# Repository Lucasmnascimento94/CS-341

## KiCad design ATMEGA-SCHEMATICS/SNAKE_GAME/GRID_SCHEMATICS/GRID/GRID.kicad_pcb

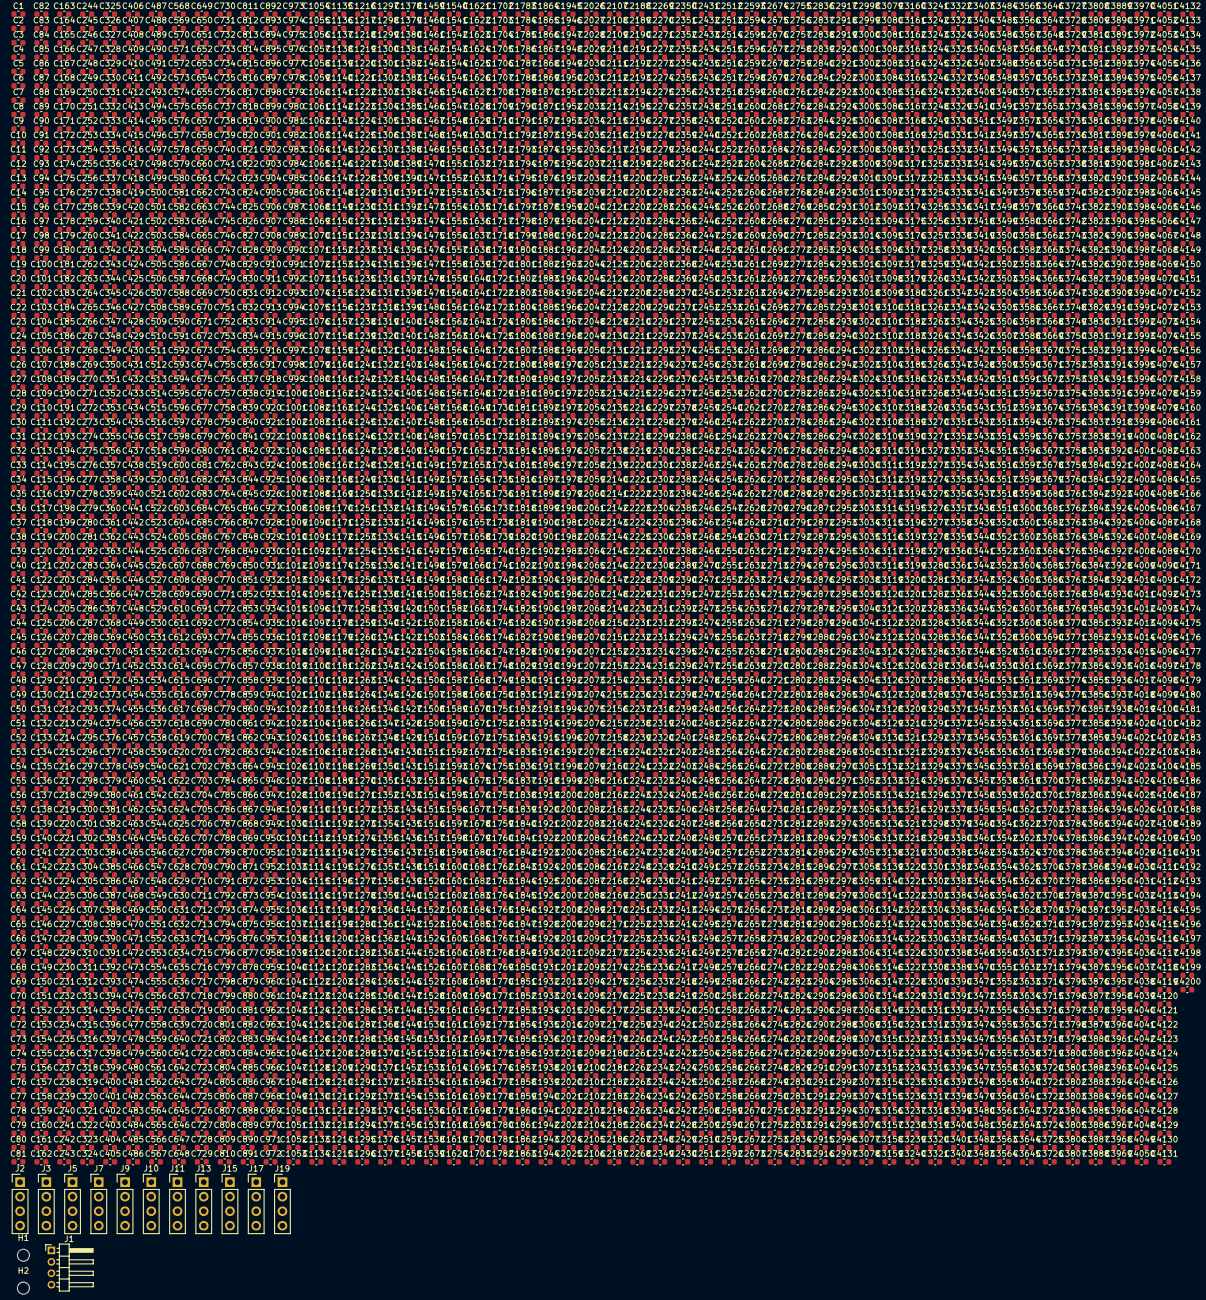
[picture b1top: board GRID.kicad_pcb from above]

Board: 4 copper layers, 4216 parts (0 on the bottom side), 13 nets, no tracks yet.

Parts (part):
C1, C2, C3, C4, C5, C6, C7, C8, C9, C10, C11, C12, C13, C14, C15, C16, C17, C18, C19, C20, C21, C22, C23, C24, C25, C26, C27, C28, C29, C30, C31, C32, C33, C34, C35, C36, C37, C38, C39, C40, C41, C42, C43, C44, C45, C46, C47, C48, C49, C50, C51, C52, C53, C54, C55, C56, C57, C58, C59, C60, C61, C62, C63, C64, C65, C66, C67, C68, C69, C70, C71, C72, C73, C74, C75, C76, C77, C78, C79, C80, C81, C82, C83, C84, C85, C86, C87, C88, C89, C90, C91, C92, C93, C94, C95, C96, C97, C98, C99, C100, C101, C102, C103, C104, C105, C106, C107, C108, C109, C110, C111, C112, C113, C114, C115, C116, C117, C118, C119, C120, C121, C122, C123, C124, C125, C126, C127, C128, C129, C130, C131, C132, C133, C134, C135, C136, C137, C138, C139, C140, C141, C142, C143, C144, C145, C146, C147, C148, C149, C150, C151, C152, C153, C154, C155, C156, C157, C158, C159, C160, C161, C162, C163, C164, C165, C166, C167, C168, C169, C170, C171, C172, C173, C174, C175, C176, C177, C178, C179, C180, C181, C182, C183, C184, C185, C186, C187, C188, C189, C190, C191, C192, C193, C194, C195, C196, C197, C198, C199, C200, C201, C202, C203, C204, C205, C206, C207, C208, C209, C210, C211, C212, C213, C214, C215, C216, C217, C218, C219, C220, C221, C222, C223, C224, C225, C226, C227, C228, C229, C230, C231, C232, C233, C234, C235, C236, C237, C238, C239, C240, C241, C242, C243, C244, C245, C246, C247, C248, C249, C250, C251, C252, C253, C254, C255, C256, C257, C258, C259, C260, C261, C262, C263, C264, C265, C266, C267, C268, C269, C270, C271, C272, C273, C274, C275, C276, C277, C278, C279, C280, C281, C282, C283, C284, C285, C286, C287, C288, C289, C290, C291, C292, C293, C294, C295, C296, C297, C298, C299, C300, C301, C302, C303, C304, C305, C306, C307, C308, C309, C310, C311, C312, C313, C314, C315, C316, C317, C318, C319, C320, C321, C322, C323, C324, C325, C326, C327, C328, C329, C330, C331, C332, C333, C334, C335, C336, C337, C338, C339, C340, C341, C342, C343, C344, C345, C346, C347, C348, C349, C350, C351, C352, C353, C354, C355, C356, C357, C358, C359, C360, C361, C362, C363, C364, C365, C366, C367, C368, C369, C370, C371, C372, C373, C374, C375, C376, C377, C378, C379, C380, C381, C382, C383, C384, C385, C386, C387, C388, C389, C390, C391, C392, C393, C394, C395, C396, C397, C398, C399, C400, C401, C402, C403, C404, C405, C406, C407, C408, C409, C410, C411, C412, C413, C414, C415, C416, C417, C418, C419, C420, C421, C422, C423, C424, C425, C426, C427, C428, C429, C430, C431, C432, C433, C434, C435, C436, C437, C438, C439, C440, C441, C442, C443, C444, C445, C446, C447, C448, C449, C450, C451, C452, C453, C454, C455, C456, C457, C458, C459, C460, C461, C462, C463, C464, C465, C466, C467, C468, C469, C470, C471, C472, C473, C474, C475, C476, C477, C478, C479, C480, C481, C482, C483, C484, C485, C486, C487, C488, C489, C490, C491, C492, C493, C494, C495, C496, C497, C498, C499, C500, C501, C502, C503, C504, C505, C506, C507, C508, C509, C510, C511, C512, C513, C514, C515, C516, C517, C518, C519, C520, C521, C522, C523, C524, C525, C526, C527, C528, C529, C530, C531, C532, C533, C534, C535, C536, C537, C538, C539, C540, C541, C542, C543, C544, C545, C546, C547, C548, C549, C550, C551, C552, C553, C554, C555, C556, C557, C558, C559, C560, C561, C562, C563, C564, C565, C566, C567, C568, C569, C570, C571, C572, C573, C574, C575, C576, C577, C578, C579, C580, C581, C582, C583, C584, C585, C586, C587, C588, C589, C590, C591, C592, C593, C594, C595, C596, C597, C598, C599, C600, C601, C602, C603, C604, C605, C606, C607, C608, C609, C610, C611, C612, C613, C614, C615, C616, C617, C618, C619, C620, C621, C622, C623, C624, C625, C626, C627, C628, C629, C630, C631, C632, C633, C634, C635, C636, C637, C638, C639, C640, C641, C642, C643, C644, C645, C646, C647, C648, C649, C650, C651, C652, C653, C654, C655, C656, C657, C658, C659, C660, C661, C662, C663, C664, C665, C666, C667, C668, C669, C670, C671, C672, C673, C674, C675, C676, C677, C678, C679, C680, C681, C682, C683, C684, C685, C686, C687, C688, C689, C690, C691, C692, C693, C694, C695, C696, C697, C698, C699, C700, C701, C702, C703, C704, C705, C706, C707, C708, C709, C710, C711, C712, C713, C714, C715, C716, C717, C718, C719, C720, C721, C722, C723, C724, C725, C726, C727, C728, C729, C730, C731, C732, C733, C734, C735, C736, C737, C738, C739, C740, C741, C742, C743, C744, C745, C746, C747, C748, C749, C750, C751, C752, C753, C754, C755, C756, C757, C758, C759, C760, C761, C762, C763, C764, C765, C766, C767, C768, C769, C770, C771, C772, C773, C774, C775, C776, C777, C778, C779, C780, C781, C782, C783, C784, C785, C786, C787, C788, C789, C790, C791, C792, C793, C794, C795, C796, C797, C798, C799, C800, C801, C802, C803, C804, C805, C806, C807, C808, C809, C810, C811, C812, C813, C814, C815, C816, C817, C818, C819, C820, C821, C822, C823, C824, C825, C826, C827, C828, C829, C830, C831, C832, C833, C834, C835, C836, C837, C838, C839, C840, C841, C842, C843, C844, C845, C846, C847, C848, C849, C850, C851, C852, C853, C854, C855, C856, C857, C858, C859, C860, C861, C862, C863, C864, C865, C866, C867, C868, C869, C870, C871, C872, C873, C874, C875, C876, C877, C878, C879, C880, C881, C882, C883, C884, C885, C886, C887, C888, C889, C890, C891, C892, C893, C894, C895, C896, C897, C898, C899, C900, C901, C902, C903, C904, C905, C906, C907, C908, C909, C910, C911, C912, C913, C914, C915, C916, C917, C918, C919, C920, C921, C922, C923, C924, C925, C926, C927, C928, C929, C930, C931, C932, C933, C934, C935, C936, C937, C938, C939, C940, C941, C942, C943, C944, C945, C946, C947, C948, C949, C950, C951, C952, C953, C954, C955, C956, C957, C958, C959, C960, C961, C962, C963, C964, C965, C966, C967, C968, C969, C970, C971, C972, C973, C974, C975, C976, C977, C978, C979, C980, C981, C982, C983, C984, C985, C986, C987, C988, C989, C990, C991, C992, C993, C994, C995, C996, C997, C998, C999, C1000, C1001, C1002, C1003, C1004, C1005, C1006, C1007, C1008, C1009, C1010, C1011, C1012, C1013, C1014, C1015, C1016, C1017, C1018, C1019, C1020, C1021, C1022, C1023, C1024, C1025, C1026, C1027, C1028, C1029, C1030, C1031, C1032, C1033, C1034, C1035, C1036, C1037, C1038, C1039, C1040, C1041, C1042, C1043, C1044, C1045, C1046, C1047, C1048, C1049, C1050, C1051, C1052, C1053, C1054, C1055, C1056, C1057, C1058, C1059, C1060, C1061, C1062, C1063, C1064, C1065, C1066, C1067, C1068, C1069, C1070, C1071, C1072, C1073, C1074, C1075, C1076, C1077, C1078, C1079, C1080, C1081, C1082, C1083, C1084, C1085, C1086, C1087, C1088, C1089, C1090, C1091, C1092, C1093, C1094, C1095, C1096, C1097, C1098, C1099, C1100, C1101, C1102, C1103, C1104, C1105, C1106, C1107, C1108, C1109, C1110, C1111, C1112, C1113, C1114, C1115, C1116, C1117, C1118, C1119, C1120, C1121, C1122, C1123, C1124, C1125, C1126, C1127, C1128, C1129, C1130, C1131, C1132, C1133, C1134, C1135, C1136, C1137, C1138, C1139, C1140, C1141, C1142, C1143, C1144, C1145, C1146, C1147, C1148, C1149, C1150, C1151, C1152, C1153, C1154, C1155, C1156, C1157, C1158, C1159, C1160, C1161, C1162, C1163, C1164, C1165, C1166, C1167, C1168, C1169, C1170, C1171, C1172, C1173, C1174, C1175, C1176, C1177, C1178, C1179, C1180, C1181, C1182, C1183, C1184, C1185, C1186, C1187, C1188, C1189, C1190, C1191, C1192, C1193, C1194, C1195, C1196, C1197, C1198, C1199, C1200, C1201, C1202, C1203, C1204, C1205, C1206, C1207, C1208, C1209, C1210, C1211, C1212, C1213, C1214, C1215, C1216, C1217, C1218, C1219, C1220, C1221, C1222, C1223, C1224, C1225, C1226, C1227, C1228, C1229, C1230, C1231, C1232, C1233, C1234, C1235, C1236, C1237, C1238, C1239, C1240, C1241, C1242, C1243, C1244, C1245, C1246, C1247, C1248, C1249, C1250, C1251, C1252, C1253, C1254, C1255, C1256, C1257, C1258, C1259, C1260, C1261, C1262, C1263, C1264, C1265, C1266, C1267, C1268, C1269, C1270, C1271, C1272, C1273, C1274, C1275, C1276, C1277, C1278, C1279, C1280, C1281, C1282, C1283, C1284, C1285, C1286, C1287, C1288, C1289, C1290, C1291, C1292, C1293, C1294, C1295, C1296, C1297, C1298, C1299, C1300, C1301, C1302, C1303, C1304, C1305, C1306, C1307, C1308, C1309, C1310, C1311, C1312, C1313, C1314, C1315, C1316, C1317, C1318, C1319, C1320, C1321, C1322, C1323, C1324, C1325, C1326, C1327, C1328, C1329, C1330, C1331, C1332, C1333, C1334, C1335, C1336, C1337, C1338, C1339, C1340, C1341, C1342, C1343, C1344, C1345, C1346, C1347, C1348, C1349, C1350, C1351, C1352, C1353, C1354, C1355, C1356, C1357, C1358, C1359, C1360, C1361, C1362, C1363, C1364, C1365, C1366, C1367, C1368, C1369, C1370, C1371, C1372, C1373, C1374, C1375, C1376, C1377, C1378, C1379, C1380, C1381, C1382, C1383, C1384, C1385, C1386, C1387, C1388, C1389, C1390, C1391, C1392, C1393, C1394, C1395, C1396, C1397, C1398, C1399, C1400, C1401, C1402, C1403, C1404, C1405, C1406, C1407, C1408, C1409, C1410, C1411, C1412, C1413, C1414, C1415, C1416, C1417, C1418, C1419, C1420, C1421, C1422, C1423, C1424, C1425, C1426, C1427, C1428, C1429, C1430, C1431, C1432, C1433, C1434, C1435, C1436, C1437, C1438, C1439, C1440, C1441, C1442, C1443, C1444, C1445, C1446, C1447, C1448, C1449, C1450, C1451, C1452, C1453, C1454, C1455, C1456, C1457, C1458, C1459, C1460, C1461, C1462, C1463, C1464, C1465, C1466, C1467, C1468, C1469, C1470, C1471, C1472, C1473, C1474, C1475, C1476, C1477, C1478, C1479, C1480, C1481, C1482, C1483, C1484, C1485, C1486, C1487, C1488, C1489, C1490, C1491, C1492, C1493, C1494, C1495, C1496, C1497, C1498, C1499, C1500, C1501, C1502, C1503, C1504, C1505, C1506, C1507, C1508, C1509, C1510, C1511, C1512, C1513, C1514, C1515, C1516, C1517, C1518, C1519, C1520, C1521, C1522, C1523, C1524, C1525, C1526, C1527, C1528, C1529, C1530, C1531, C1532, C1533, C1534, C1535, C1536, C1537, C1538, C1539, C1540, C1541, C1542, C1543, C1544, C1545, C1546, C1547, C1548, C1549, C1550, C1551, C1552, C1553, C1554, C1555, C1556, C1557, C1558, C1559, C1560, C1561, C1562, C1563, C1564, C1565, C1566, C1567, C1568, C1569, C1570, C1571, C1572, C1573, C1574, C1575, C1576, C1577, C1578, C1579, C1580, C1581, C1582, C1583, C1584, C1585, C1586, C1587, C1588, C1589, C1590, C1591, C1592, C1593, C1594, C1595, C1596, C1597, C1598, C1599, C1600, C1601, C1602, C1603, C1604, C1605, C1606, C1607, C1608, C1609, C1610, C1611, C1612, C1613, C1614, C1615, C1616, C1617, C1618, C1619, C1620, C1621, C1622, C1623, C1624, C1625, C1626, C1627, C1628, C1629, C1630, C1631, C1632, C1633, C1634, C1635, C1636, C1637, C1638, C1639, C1640, C1641, C1642, C1643, C1644, C1645, C1646, C1647, C1648, C1649, C1650, C1651, C1652, C1653, C1654, C1655, C1656, C1657, C1658, C1659, C1660, C1661, C1662, C1663, C1664, C1665, C1666, C1667, C1668, C1669, C1670, C1671, C1672, C1673, C1674, C1675, C1676, C1677, C1678, C1679, C1680, C1681, C1682, C1683, C1684, C1685, C1686, C1687, C1688, C1689, C1690, C1691, C1692, C1693, C1694, C1695, C1696, C1697, C1698, C1699, C1700, C1701, C1702, C1703, C1704, C1705, C1706, C1707, C1708, C1709, C1710, C1711, C1712, C1713, C1714, C1715, C1716, C1717, C1718, C1719, C1720, C1721, C1722, C1723, C1724, C1725, C1726, C1727, C1728, C1729, C1730, C1731, C1732, C1733, C1734, C1735, C1736, C1737, C1738, C1739, C1740, C1741, C1742, C1743, C1744, C1745, C1746, C1747, C1748, C1749, C1750, C1751, C1752, C1753, C1754, C1755, C1756, C1757, C1758, C1759, C1760, C1761, C1762, C1763, C1764, C1765, C1766, C1767, C1768, C1769, C1770, C1771, C1772, C1773, C1774, C1775, C1776, C1777, C1778, C1779, C1780, C1781, C1782, C1783, C1784, C1785, C1786, C1787, C1788, C1789, C1790, C1791, C1792, C1793, C1794, C1795, C1796, C1797, C1798, C1799, C1800, C1801, C1802, C1803, C1804, C1805, C1806, C1807, C1808, C1809, C1810, C1811, C1812, C1813, C1814, C1815, C1816, C1817, C1818, C1819, C1820, C1821, C1822, C1823, C1824, C1825, C1826, C1827, C1828, C1829, C1830, C1831, C1832, C1833, C1834, C1835, C1836, C1837, C1838, C1839, C1840, C1841, C1842, C1843, C1844, C1845, C1846, C1847, C1848, C1849, C1850, C1851, C1852, C1853, C1854, C1855, C1856, C1857, C1858, C1859, C1860, C1861, C1862, C1863, C1864, C1865, C1866, C1867, C1868, C1869, C1870, C1871, C1872, C1873, C1874, C1875, C1876, C1877, C1878, C1879, C1880, C1881, C1882, C1883, C1884, C1885, C1886, C1887, C1888, C1889, C1890, C1891, C1892, C1893, C1894, C1895, C1896, C1897, C1898, C1899, C1900, C1901, C1902, C1903, C1904, C1905, C1906, C1907, C1908, C1909, C1910, C1911, C1912, C1913, C1914, C1915, C1916, C1917, C1918, C1919, C1920, C1921, C1922, C1923, C1924, C1925, C1926, C1927, C1928, C1929, C1930, C1931, C1932, C1933, C1934, C1935, C1936, C1937, C1938, C1939, C1940, C1941, C1942, C1943, C1944, C1945, C1946, C1947, C1948, C1949, C1950, C1951, C1952, C1953, C1954, C1955, C1956, C1957, C1958, C1959, C1960, C1961, C1962, C1963, C1964, C1965, C1966, C1967, C1968, C1969, C1970, C1971, C1972, C1973, C1974, C1975, C1976, C1977, C1978, C1979, C1980, C1981, C1982, C1983, C1984, C1985, C1986, C1987, C1988, C1989, C1990, C1991, C1992, C1993, C1994, C1995, C1996, C1997, C1998, C1999, C2000, C2001, C2002,
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
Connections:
GND: C1.1, C2.1, C3.1, C4.1, C5.1, C6.1, C7.1, C8.1, C9.1, C10.1, C11.1, C12.1, C13.1, C14.1, C15.1, C16.1, C17.1, C18.1, C19.1, C20.1, C21.1, C22.1, C23.1, C24.1, C25.1, C26.1, C27.1, C28.1, C29.1, C30.1, C31.1, C32.1, C33.1, C34.1, C35.1, C36.1, C37.1, C38.1, C39.1, C40.1, C41.1, C42.1, C43.1, C44.1, C45.1, C46.1, C47.1, C48.1, C49.1, C50.1, C51.1, C52.1, C53.1, C54.1, C55.1, C56.1, C57.1, C58.1, C59.1, C60.1, C61.1, C62.1, C63.1, C64.1, C65.1, C66.1, C67.1, C68.1, C69.1, C70.1, C71.1, C72.1, C73.1, C74.1, C75.1, C76.1, C77.1, C78.1, C79.1, C80.1, C81.1, C82.1, C83.1, C84.1, C85.1, C86.1, C87.1, C88.1, C89.1, C90.1, C91.1, C92.1, C93.1, C94.1, C95.1, C96.1, C97.1, C98.1, C99.1, C100.1, C101.1, C102.1, C103.1, C104.1, C105.1, C106.1, C107.1, C108.1, C109.1, C110.1, C111.1, C112.1, C113.1, C114.1, C115.1, C116.1, C117.1, C118.1, C119.1, C120.1, C121.1, C122.1, C123.1, C124.1, C125.1, C126.1, C127.1, C128.1, C129.1, C130.1, C131.1, C132.1, C133.1, C134.1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
unnamed: J1.2, J2.2
unnamed: J1.1, J2.1
VCC_1: C1.2, C2.2, C3.2, C4.2, C5.2, C6.2, C7.2, C8.2, C9.2, C10.2, C11.2, C12.2, C13.2, C14.2, C15.2, C16.2, C17.2, C18.2, C19.2, C20.2, C21.2, C22.2, C23.2, C24.2, C25.2, C26.2, C27.2, C28.2, C29.2, C30.2, C31.2, C32.2, C33.2, C34.2, C35.2, C36.2, C37.2, C38.2, C39.2, C40.2, C41.2, C42.2, C43.2, C44.2, C45.2, C46.2, C47.2, C48.2, C49.2, C50.2, C51.2, C52.2, C53.2, C54.2, C55.2, C56.2, C57.2, C58.2, C59.2, C60.2, C61.2, C62.2, C63.2, C64.2, C65.2, C66.2, C67.2, C68.2, C69.2, C70.2, C71.2, C72.2, C73.2, C74.2, C75.2, C76.2, C77.2, C78.2, C79.2, C80.2, C81.2, C82.2, C83.2, C84.2, C85.2, C86.2, C87.2, C88.2, C89.2, C90.2, C91.2, C92.2, C93.2, C94.2, C95.2, C96.2, C97.2, C98.2, C99.2, C100.2, C101.2, C102.2, C103.2, C104.2, C105.2, C106.2, C107.2, C108.2, C109.2, C110.2, C111.2, C112.2, C113.2, C114.2, C115.2, C116.2, C117.2, C118.2, C119.2, C120.2, C121.2, C122.2, C123.2, C124.2, C125.2, C126.2, C127.2, C128.2, C129.2, C130.2, C131.2, C132.2, C133.2, C134.2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
VCC_2: C421.2, C422.2, C423.2, C424.2, C425.2, C426.2, C427.2, C428.2, C429.2, C430.2, C431.2, C432.2, C433.2, C434.2, C435.2, C436.2, C437.2, C438.2, C439.2, C440.2, C441.2, C442.2, C443.2, C444.2, C445.2, C446.2, C447.2, C448.2, C449.2, C450.2, C451.2, C452.2, C453.2, C454.2, C455.2, C456.2, C457.2, C458.2, C459.2, C460.2, C461.2, C462.2, C463.2, C464.2, C465.2, C466.2, C467.2, C468.2, C469.2, C470.2, C471.2, C472.2, C473.2, C474.2, C475.2, C476.2, C477.2, C478.2, C479.2, C480.2, C481.2, C482.2, C483.2, C484.2, C485.2, C486.2, C487.2, C488.2, C489.2, C490.2, C491.2, C492.2, C493.2, C494.2, C495.2, C496.2, C497.2, C498.2, C499.2, C500.2, C501.2, C502.2, C503.2, C504.2, C505.2, C506.2, C507.2, C508.2, C509.2, C510.2, C511.2, C512.2, C513.2, C514.2, C515.2, C516.2, C517.2, C518.2, C519.2, C520.2, C521.2, C522.2, C523.2, C524.2, C525.2, C526.2, C527.2, C528.2, C529.2, C530.2, C531.2, C532.2, C533.2, C534.2, C535.2, C536.2, C537.2, C538.2, C539.2, C540.2, C541.2, C542.2, C543.2, C544.2, C545.2, C546.2, C547.2, C548.2, C549.2, C550.2, C551.2, C552.2, C553.2, C554.2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
VCC_3: C841.2, C842.2, C843.2, C844.2, C845.2, C846.2, C847.2, C848.2, C849.2, C850.2, C851.2, C852.2, C853.2, C854.2, C855.2, C856.2, C857.2, C858.2, C859.2, C860.2, C861.2, C862.2, C863.2, C864.2, C865.2, C866.2, C867.2, C868.2, C869.2, C870.2, C871.2, C872.2, C873.2, C874.2, C875.2, C876.2, C877.2, C878.2, C879.2, C880.2, C881.2, C882.2, C883.2, C884.2, C885.2, C886.2, C887.2, C888.2, C889.2, C890.2, C891.2, C892.2, C893.2, C894.2, C895.2, C896.2, C897.2, C898.2, C899.2, C900.2, C901.2, C902.2, C903.2, C904.2, C905.2, C906.2, C907.2, C908.2, C909.2, C910.2, C911.2, C912.2, C913.2, C914.2, C915.2, C916.2, C917.2, C918.2, C919.2, C920.2, C921.2, C922.2, C923.2, C924.2, C925.2, C926.2, C927.2, C928.2, C929.2, C930.2, C931.2, C932.2, C933.2, C934.2, C935.2, C936.2, C937.2, C938.2, C939.2, C940.2, C941.2, C942.2, C943.2, C944.2, C945.2, C946.2, C947.2, C948.2, C949.2, C950.2, C951.2, C952.2, C953.2, C954.2, C955.2, C956.2, C957.2, C958.2, C959.2, C960.2, C961.2, C962.2, C963.2, C964.2, C965.2, C966.2, C967.2, C968.2, C969.2, C970.2, C971.2, C972.2, C973.2, C974.2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
VCC_4: C1261.2, C1262.2, C1263.2, C1264.2, C1265.2, C1266.2, C1267.2, C1268.2, C1269.2, C1270.2, C1271.2, C1272.2, C1273.2, C1274.2, C1275.2, C1276.2, C1277.2, C1278.2, C1279.2, C1280.2, C1281.2, C1282.2, C1283.2, C1284.2, C1285.2, C1286.2, C1287.2, C1288.2, C1289.2, C1290.2, C1291.2, C1292.2, C1293.2, C1294.2, C1295.2, C1296.2, C1297.2, C1298.2, C1299.2, C1300.2, C1301.2, C1302.2, C1303.2, C1304.2, C1305.2, C1306.2, C1307.2, C1308.2, C1309.2, C1310.2, C1311.2, C1312.2, C1313.2, C1314.2, C1315.2, C1316.2, C1317.2, C1318.2, C1319.2, C1320.2, C1321.2, C1322.2, C1323.2, C1324.2, C1325.2, C1326.2, C1327.2, C1328.2, C1329.2, C1330.2, C1331.2, C1332.2, C1333.2, C1334.2, C1335.2, C1336.2, C1337.2, C1338.2, C1339.2, C1340.2, C1341.2, C1342.2, C1343.2, C1344.2, C1345.2, C1346.2, C1347.2, C1348.2, C1349.2, C1350.2, C1351.2, C1352.2, C1353.2, C1354.2, C1355.2, C1356.2, C1357.2, C1358.2, C1359.2, C1360.2, C1361.2, C1362.2, C1363.2, C1364.2, C1365.2, C1366.2, C1367.2, C1368.2, C1369.2, C1370.2, C1371.2, C1372.2, C1373.2, C1374.2, C1375.2, C1376.2, C1377.2, C1378.2, C1379.2, C1380.2, C1381.2, C1382.2, C1383.2, C1384.2, C1385.2, C1386.2, C1387.2, C1388.2, C1389.2, C1390.2, C1391.2, C1392.2, C1393.2, C1394.2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
VCC_5: C1681.2, C1682.2, C1683.2, C1684.2, C1685.2, C1686.2, C1687.2, C1688.2, C1689.2, C1690.2, C1691.2, C1692.2, C1693.2, C1694.2, C1695.2, C1696.2, C1697.2, C1698.2, C1699.2, C1700.2, C1701.2, C1702.2, C1703.2, C1704.2, C1705.2, C1706.2, C1707.2, C1708.2, C1709.2, C1710.2, C1711.2, C1712.2, C1713.2, C1714.2, C1715.2, C1716.2, C1717.2, C1718.2, C1719.2, C1720.2, C1721.2, C1722.2, C1723.2, C1724.2, C1725.2, C1726.2, C1727.2, C1728.2, C1729.2, C1730.2, C1731.2, C1732.2, C1733.2, C1734.2, C1735.2, C1736.2, C1737.2, C1738.2, C1739.2, C1740.2, C1741.2, C1742.2, C1743.2, C1744.2, C1745.2, C1746.2, C1747.2, C1748.2, C1749.2, C1750.2, C1751.2, C1752.2, C1753.2, C1754.2, C1755.2, C1756.2, C1757.2, C1758.2, C1759.2, C1760.2, C1761.2, C1762.2, C1763.2, C1764.2, C1765.2, C1766.2, C1767.2, C1768.2, C1769.2, C1770.2, C1771.2, C1772.2, C1773.2, C1774.2, C1775.2, C1776.2, C1777.2, C1778.2, C1779.2, C1780.2, C1781.2, C1782.2, C1783.2, C1784.2, C1785.2, C1786.2, C1787.2, C1788.2, C1789.2, C1790.2, C1791.2, C1792.2, C1793.2, C1794.2, C1795.2, C1796.2, C1797.2, C1798.2, C1799.2, C1800.2, C1801.2, C1802.2, C1803.2, C1804.2, C1805.2, C1806.2, C1807.2, C1808.2, C1809.2, C1810.2, C1811.2, C1812.2, C1813.2, C1814.2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
VCC_6: C2101.2, C2102.2, C2103.2, C2104.2, C2105.2, C2106.2, C2107.2, C2108.2, C2109.2, C2110.2, C2111.2, C2112.2, C2113.2, C2114.2, C2115.2, C2116.2, C2117.2, C2118.2, C2119.2, C2120.2, C2121.2, C2122.2, C2123.2, C2124.2, C2125.2, C2126.2, C2127.2, C2128.2, C2129.2, C2130.2, C2131.2, C2132.2, C2133.2, C2134.2, C2135.2, C2136.2, C2137.2, C2138.2, C2139.2, C2140.2, C2141.2, C2142.2, C2143.2, C2144.2, C2145.2, C2146.2, C2147.2, C2148.2, C2149.2, C2150.2, C2151.2, C2152.2, C2153.2, C2154.2, C2155.2, C2156.2, C2157.2, C2158.2, C2159.2, C2160.2, C2161.2, C2162.2, C2163.2, C2164.2, C2165.2, C2166.2, C2167.2, C2168.2, C2169.2, C2170.2, C2171.2, C2172.2, C2173.2, C2174.2, C2175.2, C2176.2, C2177.2, C2178.2, C2179.2, C2180.2, C2181.2, C2182.2, C2183.2, C2184.2, C2185.2, C2186.2, C2187.2, C2188.2, C2189.2, C2190.2, C2191.2, C2192.2, C2193.2, C2194.2, C2195.2, C2196.2, C2197.2, C2198.2, C2199.2, C2200.2, C2201.2, C2202.2, C2203.2, C2204.2, C2205.2, C2206.2, C2207.2, C2208.2, C2209.2, C2210.2, C2211.2, C2212.2, C2213.2, C2214.2, C2215.2, C2216.2, C2217.2, C2218.2, C2219.2, C2220.2, C2221.2, C2222.2, C2223.2, C2224.2, C2225.2, C2226.2, C2227.2, C2228.2, C2229.2, C2230.2, C2231.2, C2232.2, C2233.2, C2234.2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
VCC_7: C2521.2, C2522.2, C2523.2, C2524.2, C2525.2, C2526.2, C2527.2, C2528.2, C2529.2, C2530.2, C2531.2, C2532.2, C2533.2, C2534.2, C2535.2, C2536.2, C2537.2, C2538.2, C2539.2, C2540.2, C2541.2, C2542.2, C2543.2, C2544.2, C2545.2, C2546.2, C2547.2, C2548.2, C2549.2, C2550.2, C2551.2, C2552.2, C2553.2, C2554.2, C2555.2, C2556.2, C2557.2, C2558.2, C2559.2, C2560.2, C2561.2, C2562.2, C2563.2, C2564.2, C2565.2, C2566.2, C2567.2, C2568.2, C2569.2, C2570.2, C2571.2, C2572.2, C2573.2, C2574.2, C2575.2, C2576.2, C2577.2, C2578.2, C2579.2, C2580.2, C2581.2, C2582.2, C2583.2, C2584.2, C2585.2, C2586.2, C2587.2, C2588.2, C2589.2, C2590.2, C2591.2, C2592.2, C2593.2, C2594.2, C2595.2, C2596.2, C2597.2, C2598.2, C2599.2, C2600.2, C2601.2, C2602.2, C2603.2, C2604.2, C2605.2, C2606.2, C2607.2, C2608.2, C2609.2, C2610.2, C2611.2, C2612.2, C2613.2, C2614.2, C2615.2, C2616.2, C2617.2, C2618.2, C2619.2, C2620.2, C2621.2, C2622.2, C2623.2, C2624.2, C2625.2, C2626.2, C2627.2, C2628.2, C2629.2, C2630.2, C2631.2, C2632.2, C2633.2, C2634.2, C2635.2, C2636.2, C2637.2, C2638.2, C2639.2, C2640.2, C2641.2, C2642.2, C2643.2, C2644.2, C2645.2, C2646.2, C2647.2, C2648.2, C2649.2, C2650.2, C2651.2, C2652.2, C2653.2, C2654.2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
VCC_8: C2941.2, C2942.2, C2943.2, C2944.2, C2945.2, C2946.2, C2947.2, C2948.2, C2949.2, C2950.2, C2951.2, C2952.2, C2953.2, C2954.2, C2955.2, C2956.2, C2957.2, C2958.2, C2959.2, C2960.2, C2961.2, C2962.2, C2963.2, C2964.2, C2965.2, C2966.2, C2967.2, C2968.2, C2969.2, C2970.2, C2971.2, C2972.2, C2973.2, C2974.2, C2975.2, C2976.2, C2977.2, C2978.2, C2979.2, C2980.2, C2981.2, C2982.2, C2983.2, C2984.2, C2985.2, C2986.2, C2987.2, C2988.2, C2989.2, C2990.2, C2991.2, C2992.2, C2993.2, C2994.2, C2995.2, C2996.2, C2997.2, C2998.2, C2999.2, C3000.2, C3001.2, C3002.2, C3003.2, C3004.2, C3005.2, C3006.2, C3007.2, C3008.2, C3009.2, C3010.2, C3011.2, C3012.2, C3013.2, C3014.2, C3015.2, C3016.2, C3017.2, C3018.2, C3019.2, C3020.2, C3021.2, C3022.2, C3023.2, C3024.2, C3025.2, C3026.2, C3027.2, C3028.2, C3029.2, C3030.2, C3031.2, C3032.2, C3033.2, C3034.2, C3035.2, C3036.2, C3037.2, C3038.2, C3039.2, C3040.2, C3041.2, C3042.2, C3043.2, C3044.2, C3045.2, C3046.2, C3047.2, C3048.2, C3049.2, C3050.2, C3051.2, C3052.2, C3053.2, C3054.2, C3055.2, C3056.2, C3057.2, C3058.2, C3059.2, C3060.2, C3061.2, C3062.2, C3063.2, C3064.2, C3065.2, C3066.2, C3067.2, C3068.2, C3069.2, C3070.2, C3071.2, C3072.2, C3073.2, C3074.2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
VCC_9: C3361.2, C3362.2, C3363.2, C3364.2, C3365.2, C3366.2, C3367.2, C3368.2, C3369.2, C3370.2, C3371.2, C3372.2, C3373.2, C3374.2, C3375.2, C3376.2, C3377.2, C3378.2, C3379.2, C3380.2, C3381.2, C3382.2, C3383.2, C3384.2, C3385.2, C3386.2, C3387.2, C3388.2, C3389.2, C3390.2, C3391.2, C3392.2, C3393.2, C3394.2, C3395.2, C3396.2, C3397.2, C3398.2, C3399.2, C3400.2, C3401.2, C3402.2, C3403.2, C3404.2, C3405.2, C3406.2, C3407.2, C3408.2, C3409.2, C3410.2, C3411.2, C3412.2, C3413.2, C3414.2, C3415.2, C3416.2, C3417.2, C3418.2, C3419.2, C3420.2, C3421.2, C3422.2, C3423.2, C3424.2, C3425.2, C3426.2, C3427.2, C3428.2, C3429.2, C3430.2, C3431.2, C3432.2, C3433.2, C3434.2, C3435.2, C3436.2, C3437.2, C3438.2, C3439.2, C3440.2, C3441.2, C3442.2, C3443.2, C3444.2, C3445.2, C3446.2, C3447.2, C3448.2, C3449.2, C3450.2, C3451.2, C3452.2, C3453.2, C3454.2, C3455.2, C3456.2, C3457.2, C3458.2, C3459.2, C3460.2, C3461.2, C3462.2, C3463.2, C3464.2, C3465.2, C3466.2, C3467.2, C3468.2, C3469.2, C3470.2, C3471.2, C3472.2, C3473.2, C3474.2, C3475.2, C3476.2, C3477.2, C3478.2, C3479.2, C3480.2, C3481.2, C3482.2, C3483.2, C3484.2, C3485.2, C3486.2, C3487.2, C3488.2, C3489.2, C3490.2, C3491.2, C3492.2, C3493.2, C3494.2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
VCC_10: C3781.2, C3782.2, C3783.2, C3784.2, C3785.2, C3786.2, C3787.2, C3788.2, C3789.2, C3790.2, C3791.2, C3792.2, C3793.2, C3794.2, C3795.2, C3796.2, C3797.2, C3798.2, C3799.2, C3800.2, C3801.2, C3802.2, C3803.2, C3804.2, C3805.2, C3806.2, C3807.2, C3808.2, C3809.2, C3810.2, C3811.2, C3812.2, C3813.2, C3814.2, C3815.2, C3816.2, C3817.2, C3818.2, C3819.2, C3820.2, C3821.2, C3822.2, C3823.2, C3824.2, C3825.2, C3826.2, C3827.2, C3828.2, C3829.2, C3830.2, C3831.2, C3832.2, C3833.2, C3834.2, C3835.2, C3836.2, C3837.2, C3838.2, C3839.2, C3840.2, C3841.2, C3842.2, C3843.2, C3844.2, C3845.2, C3846.2, C3847.2, C3848.2, C3849.2, C3850.2, C3851.2, C3852.2, C3853.2, C3854.2, C3855.2, C3856.2, C3857.2, C3858.2, C3859.2, C3860.2, C3861.2, C3862.2, C3863.2, C3864.2, C3865.2, C3866.2, C3867.2, C3868.2, C3869.2, C3870.2, C3871.2, C3872.2, C3873.2, C3874.2, C3875.2, C3876.2, C3877.2, C3878.2, C3879.2, C3880.2, C3881.2, C3882.2, C3883.2, C3884.2, C3885.2, C3886.2, C3887.2, C3888.2, C3889.2, C3890.2, C3891.2, C3892.2, C3893.2, C3894.2, C3895.2, C3896.2, C3897.2, C3898.2, C3899.2, C3900.2, C3901.2, C3902.2, C3903.2, C3904.2, C3905.2, C3906.2, C3907.2, C3908.2, C3909.2, C3910.2, C3911.2, C3912.2, C3913.2, C3914.2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

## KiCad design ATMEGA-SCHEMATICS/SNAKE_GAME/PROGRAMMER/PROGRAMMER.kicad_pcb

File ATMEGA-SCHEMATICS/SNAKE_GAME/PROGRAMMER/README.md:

## Installation
1. [Driver](https://ftdichip.com/drivers/d2xx-drivers/)
2. Python package to run Python script and commands[PyFtdi](https://eblot.github.io/pyftdi/)
3. USB driver installtion for Windows, idk about Linux [Zadig](https://zadig.akeo.ie/)
    * To locate the device, make sure to use libusbK

----------------
## Commands
1. ```python -c "from pyftdi.ftdi import Ftdi; Ftdi.show_devices()"``` -> Shows connected devices
2.```python ftconf.py ftdi://ftdi:232:A50285BI/1 -o eeprom_config.ini``` -> Outputs the EEPROM configuration into "eeprom_config.ini"
3. ```python ftconf.py ftdi://ftdi:232:A50285BI/1 -c?``` -> Lists all supported configuration parameters in EEPROM
4. ```python ftconf.py ftdi://ftdi:232:A50285BI/1 -c [name_of_the_pin]:?``` -> Shows all configuration values
5. ```python ftconf.py --help``` -> For EXTRA HELP
6. ``````python ftconf.py ftdi://ftdi:232:A50285BI/1 -c cbus_func_0:CLK6 -c cbus_func_1:TXLED -c cbus_func_2:RXLED -c cbus_func_3:GPIO -u``` -> configure the pins in EEPROM, and update it (MAKE SURE TO INCLUDE ```-u``` or it wont update the EEPROM)
----------------

## FYI
```./Converter_Code/Show_Devices.py``` shows connected devices (same as 1 - command)
```./Converter_Code/EEPROM.py``` prints out the current EEPROM configuration
```./current_config.ini``` is the output file of the current EEPROM configuration by using this comm

## Useful sources:
[EEPROM Management](https://eblot.github.io/pyftdi/eeprom.html)
[Programmer Guide](https://ftdichip.com/wp-content/uploads/2023/09/D2XX_Programmers_Guide.pdf) (I think this is something you would use a lot)

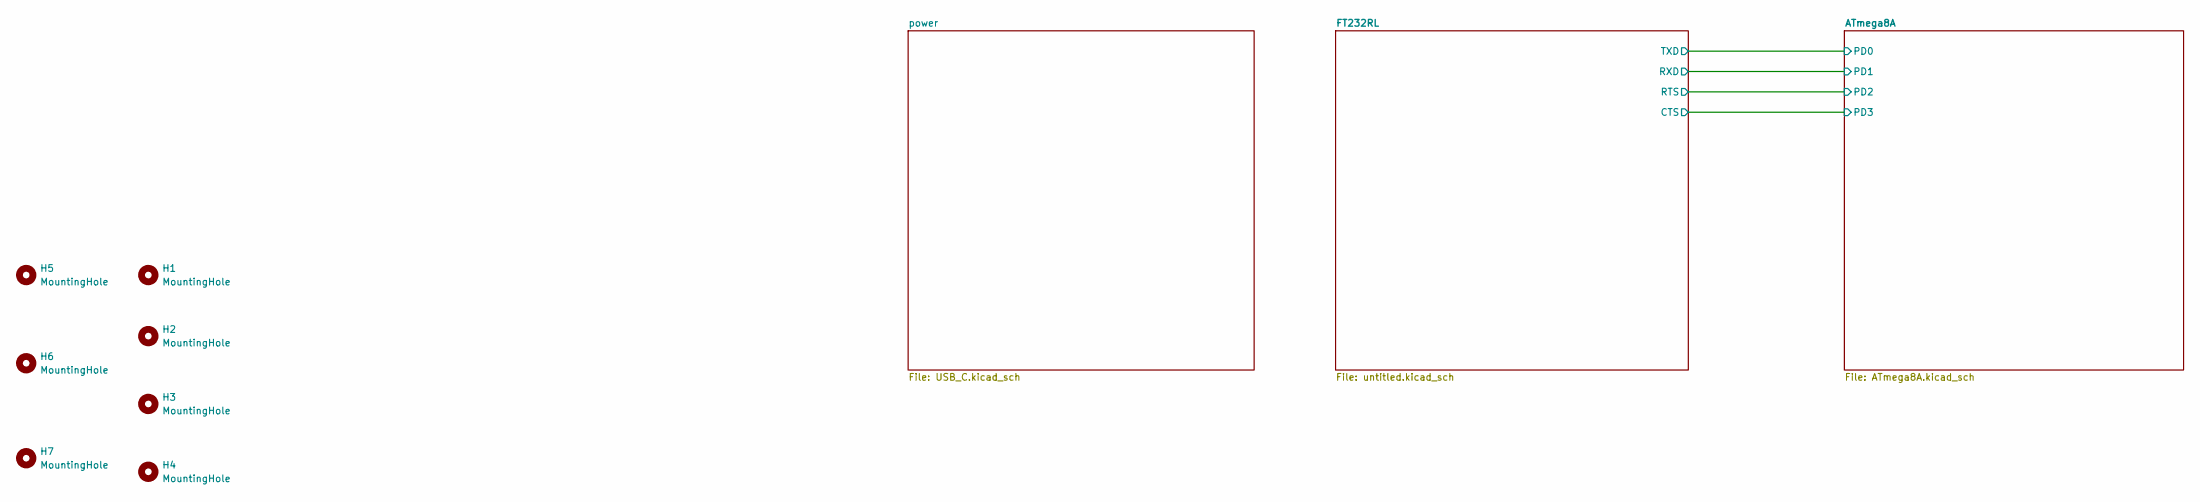
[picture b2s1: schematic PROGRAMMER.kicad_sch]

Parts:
H1, H2, H3, H4, H5, H6, H7: MountingHole; MountingHole_3.2mm_M3

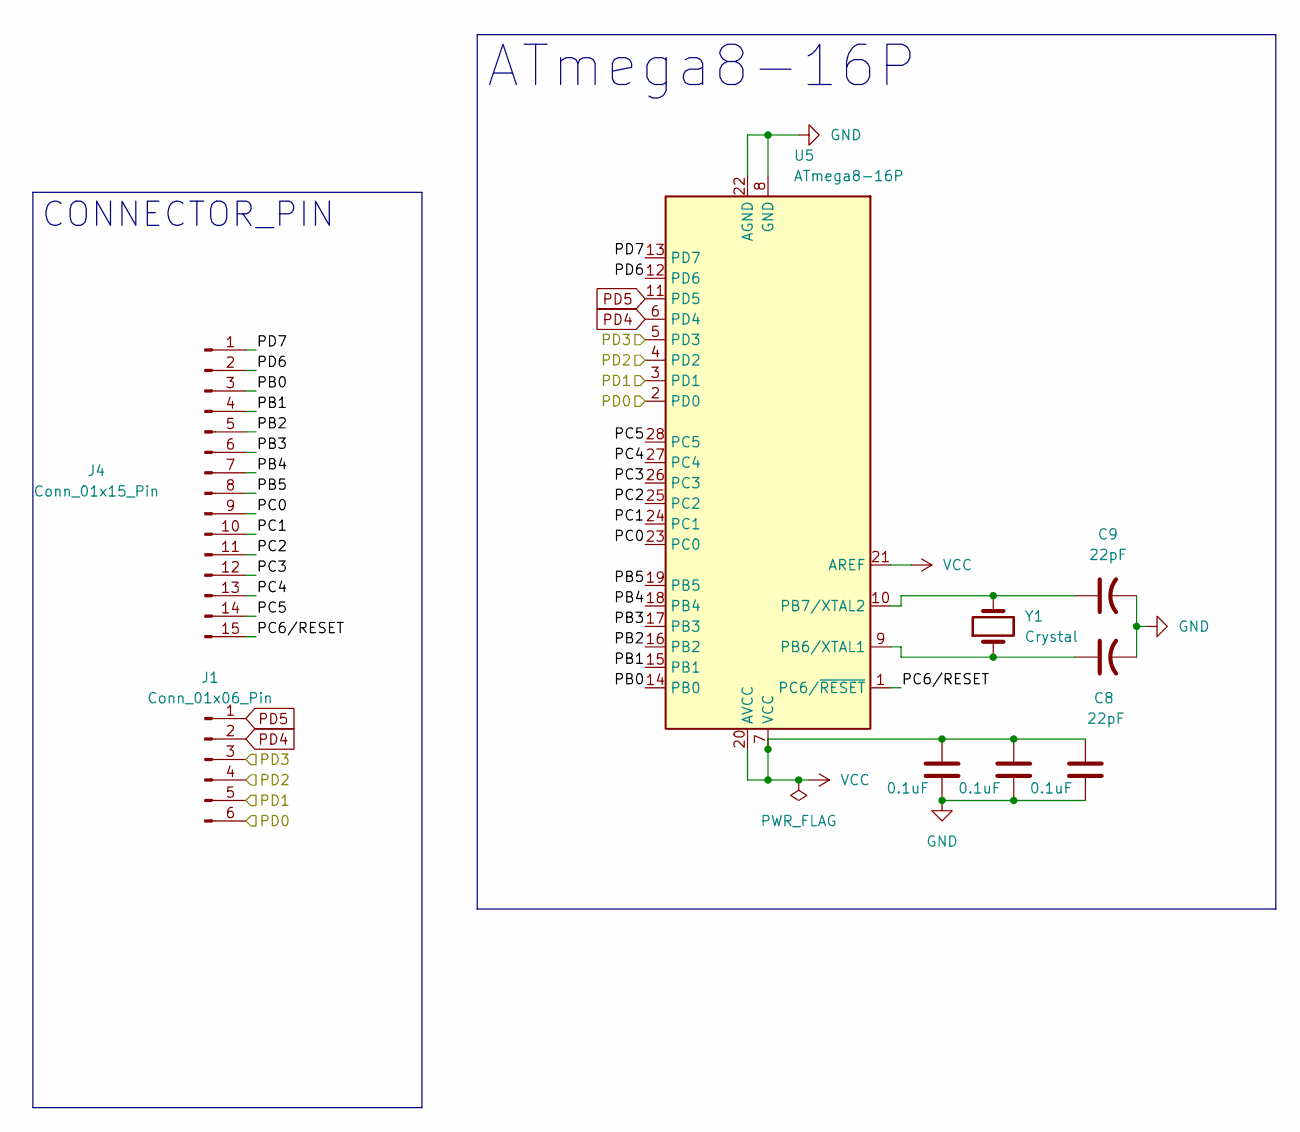
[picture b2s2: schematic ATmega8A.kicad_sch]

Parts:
C8, C9: 22pF; CP_Radial_D5.0mm_P2.50mm
C11, C12, C13: 0.1uF; C_Disc_D7.5mm_W5.0mm_P5.00mm
J1: Conn_01x06_Pin; PinHeader_1x07_P2.54mm_Vertical
J4: Conn_01x15_Pin; PinHeader_1x15_P2.54mm_Vertical
U5: ATmega8-16P; DIP-28_W7.62mm
Y1: Crystal; Resonator-2Pin_W6.0mm_H3.0mm

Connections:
/ATmega8A/PB0: J4.3, U5.14 (PB0)
/ATmega8A/PB1: J4.4, U5.15 (PB1)
/ATmega8A/PB2: J4.5, U5.16 (PB2)
/ATmega8A/PB3: J4.6, U5.17 (PB3)
/ATmega8A/PB4: J4.7, U5.18 (PB4)
/ATmega8A/PB5: J4.8, U5.19 (PB5)
/ATmega8A/PC0: J4.9, U5.23 (PC0)
/ATmega8A/PC1: J4.10, U5.24 (PC1)
/ATmega8A/PC2: J4.11, U5.25 (PC2)
/ATmega8A/PC3: J4.12, U5.26 (PC3)
/ATmega8A/PC4: J4.13, U5.27 (PC4)
/ATmega8A/PC5: J4.14, U5.28 (PC5)
/ATmega8A/PC6/RESET: J4.15, U5.1 (PC6/~RESET)
/ATmega8A/PD0: J1.6, U5.2 (PD0); also elsewhere on the board
/ATmega8A/PD1: J1.5, U5.3 (PD1); also elsewhere on the board
/ATmega8A/PD2: J1.4, U5.4 (PD2); also elsewhere on the board
/ATmega8A/PD3: J1.3, U5.5 (PD3); also elsewhere on the board
/ATmega8A/PD6: J4.2, U5.12 (PD6)
/ATmega8A/PD7: J4.1, U5.13 (PD7)
GND: C8.2, C9.2, C11.2, C12.2, C13.2, U5.8 (GND), U5.22 (AGND); also elsewhere on the board
unnamed: C8.1, U5.9 (PB6/XTAL1), Y1.1
unnamed: C9.1, U5.10 (PB7/XTAL2), Y1.2
PD4: J1.2, U5.6 (PD4); also elsewhere on the board
PD5: J1.1, U5.11 (PD5); also elsewhere on the board
VCC: C11.1, C12.1, C13.1, U5.7 (VCC), U5.20 (AVCC), U5.21 (AREF); also elsewhere on the board

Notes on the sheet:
ATmega8-16P
CONNECTOR_PIN

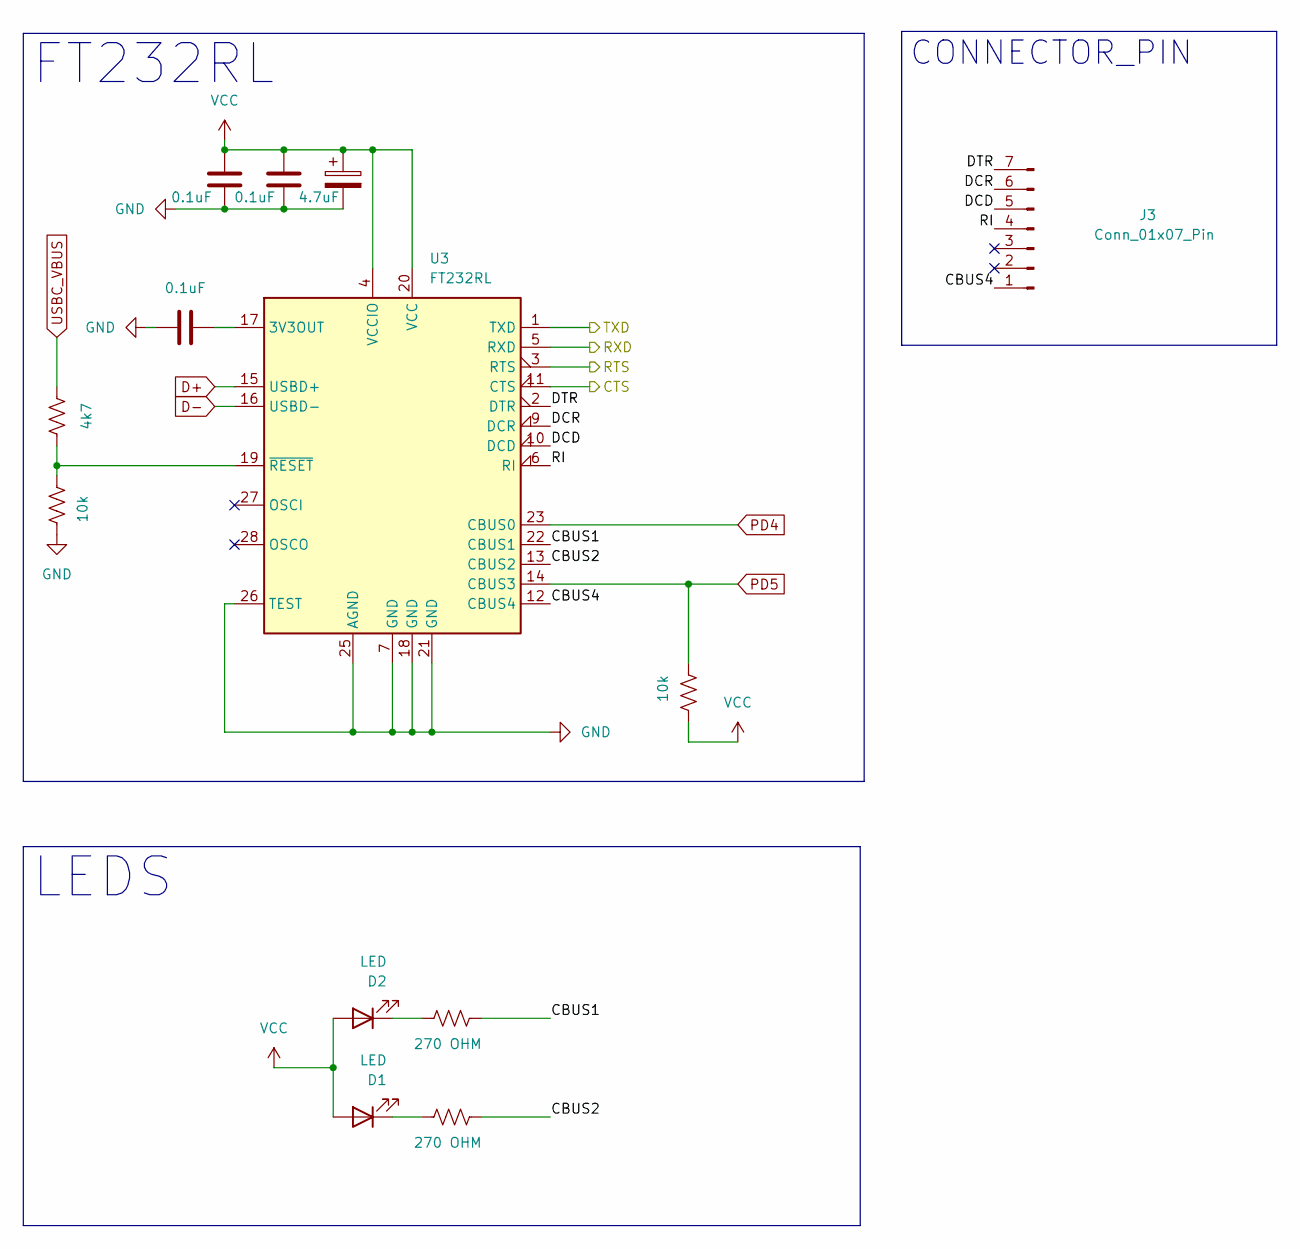
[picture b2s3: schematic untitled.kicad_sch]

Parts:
C1: 4.7uF; C_Disc_D3.0mm_W1.6mm_P2.50mm
C3, C4, C5: 0.1uF; C_Disc_D7.5mm_W5.0mm_P5.00mm
D1, D2: LED; LED_D1.8mm_W3.3mm_H2.4mm
J3: Conn_01x07_Pin; PinHeader_1x07_P2.54mm_Vertical
R4: 4k7; R_Axial_DIN0207_L6.3mm_D2.5mm_P10.16mm_Horizontal
R6, R7: 10k; R_Axial_DIN0207_L6.3mm_D2.5mm_P10.16mm_Horizontal
R8, R9: 270 OHM; R_Axial_DIN0207_L6.3mm_D2.5mm_P10.16mm_Horizontal
U3: FT232RL; DIP-28_W7.62mm

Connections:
/ATmega8A/PD0: U3.1 (TXD); also elsewhere on the board
/ATmega8A/PD1: U3.5 (RXD); also elsewhere on the board
/ATmega8A/PD2: U3.3 (RTS); also elsewhere on the board
/ATmega8A/PD3: U3.11 (CTS); also elsewhere on the board
/FT232RL/CBUS1: R9.1, U3.22 (CBUS1)
/FT232RL/CBUS2: R8.1, U3.13 (CBUS2)
/FT232RL/CBUS4: J3.1, U3.12 (CBUS4)
/FT232RL/DCD: J3.5, U3.10 (DCD)
/FT232RL/DCR: J3.6, U3.9 (DCR)
/FT232RL/DTR: J3.7, U3.2 (DTR)
/FT232RL/RI: J3.4, U3.6 (RI)
D+: U3.15 (USBD+); also elsewhere on the board
D-: U3.16 (USBD-); also elsewhere on the board
GND: C1.2, C3.1, C4.2, C5.1, R6.2, U3.7 (GND), U3.18 (GND), U3.21 (GND), U3.25 (AGND), U3.26 (TEST); also elsewhere on the board
unnamed: D1.1 (K), R8.2
unnamed: D2.1 (K), R9.2
unnamed: C3.2, U3.17 (3V3OUT)
unnamed: R4.2, R6.1, U3.19 (~RESET)
PD4: U3.23 (CBUS0); also elsewhere on the board
PD5: R7.2, U3.14 (CBUS3); also elsewhere on the board
USBC_VBUS: R4.1; also elsewhere on the board
VCC: C1.1, C4.1, C5.2, D1.2 (A), D2.2 (A), R7.1, U3.4 (VCCIO), U3.20 (VCC); also elsewhere on the board

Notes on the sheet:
LEDS
FT232RL
CONNECTOR_PIN

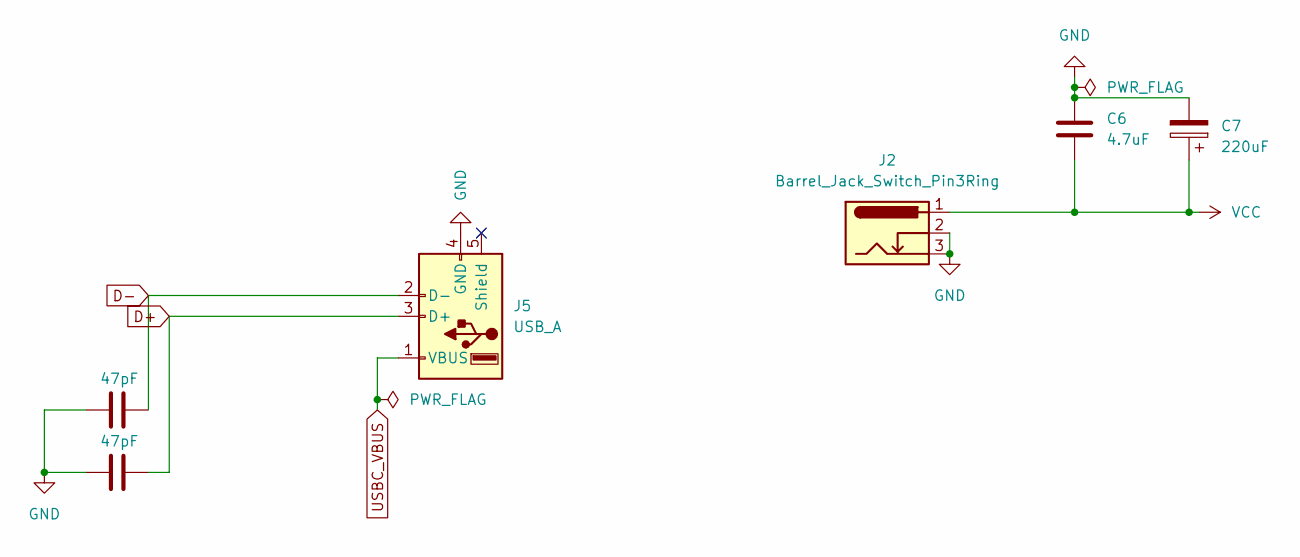
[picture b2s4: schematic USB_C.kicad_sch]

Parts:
C6: 4.7uF; C_Disc_D7.5mm_W5.0mm_P5.00mm
C7: 220uF; C_Disc_D3.0mm_W1.6mm_P2.50mm
C14, C15: 47pF; C_Disc_D7.5mm_W5.0mm_P5.00mm
J2: Barrel_Jack_Switch_Pin3Ring; BarrelJack_Horizontal
J5: USB_A; USB_A_Connfly_DS1095

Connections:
D+: C15.2, J5.3 (D+); also elsewhere on the board
D-: C14.2, J5.2 (D-); also elsewhere on the board
GND: C6.1, C7.2, C14.1, C15.1, J2.2, J2.3, J5.4 (GND); also elsewhere on the board
USBC_VBUS: J5.1 (VBUS); also elsewhere on the board
VCC: C6.2, C7.1, J2.1; also elsewhere on the board

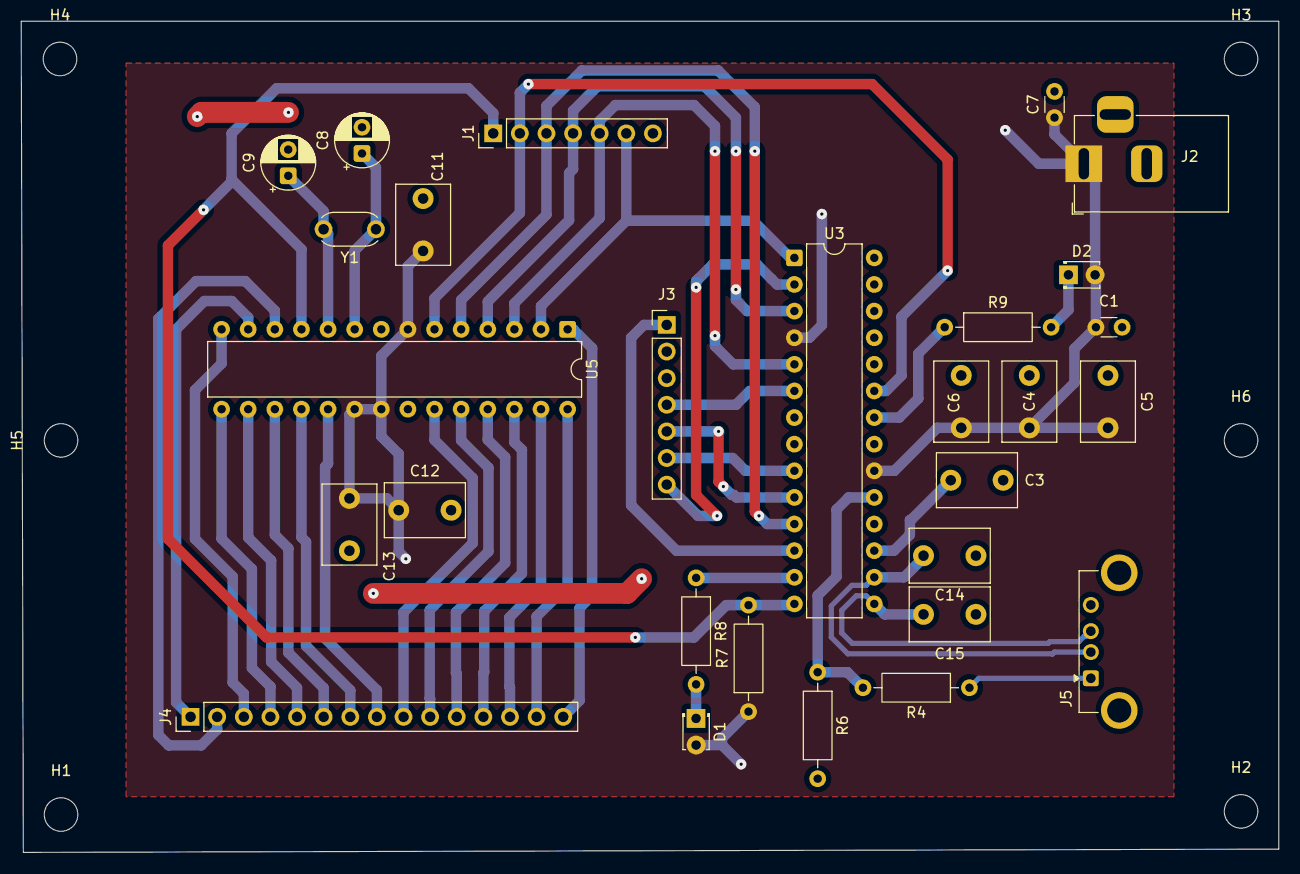
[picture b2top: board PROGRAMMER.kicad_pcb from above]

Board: 2 copper layers, 120.0 x 79.3 mm, 34 parts (0 on the bottom side), 39 nets.
